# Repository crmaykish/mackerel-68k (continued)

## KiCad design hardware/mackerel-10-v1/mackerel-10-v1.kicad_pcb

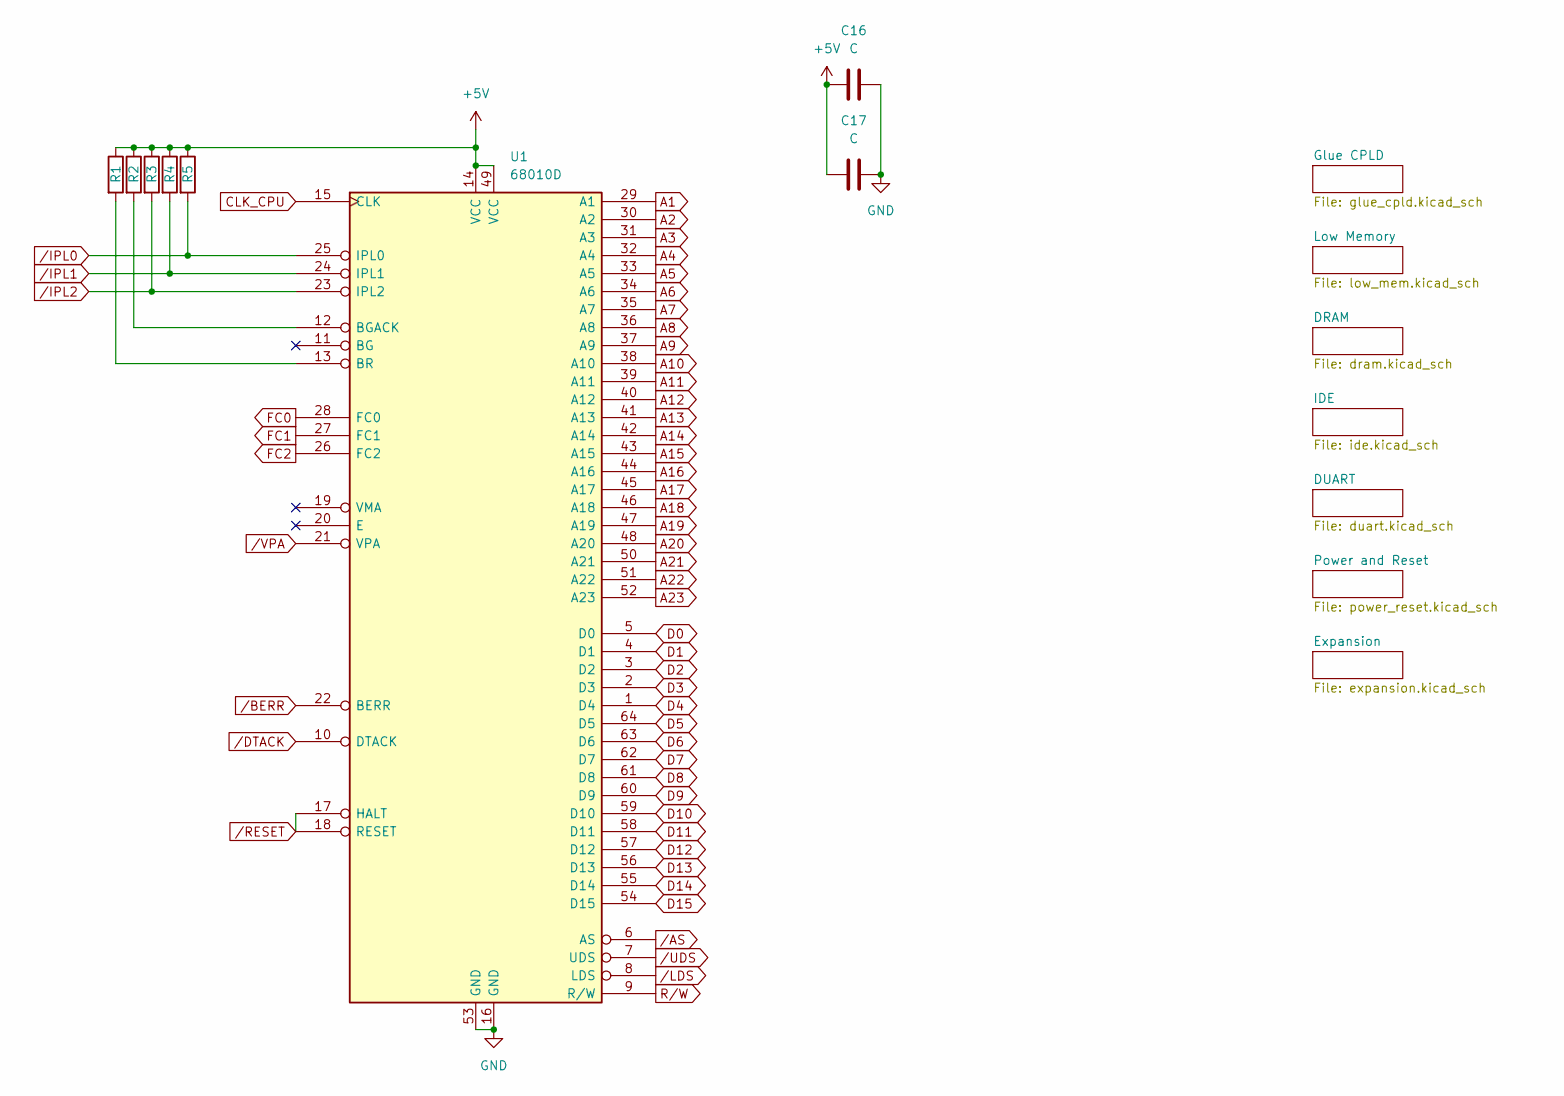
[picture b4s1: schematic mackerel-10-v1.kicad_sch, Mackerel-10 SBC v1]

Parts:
C16, C17: C; C_Disc_D4.3mm_W1.9mm_P5.00mm
R1, R2, R3, R4, R5: R; R_Axial_DIN0207_L6.3mm_D2.5mm_P7.62mm_Horizontal
U1: 68010D; DIP-64_W22.86mm

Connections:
+5V: C16.1, C17.1, R1.1, R2.1, R3.1, R4.1, R5.1, U1.14 (VCC), U1.49 (VCC); also elsewhere on the board
A1: U1.29 (A1); also elsewhere on the board
A2: U1.30 (A2); also elsewhere on the board
A3: U1.31 (A3); also elsewhere on the board
A4: U1.32 (A4); also elsewhere on the board
A5: U1.33 (A5); also elsewhere on the board
A6: U1.34 (A6); also elsewhere on the board
A7: U1.35 (A7); also elsewhere on the board
A8: U1.36 (A8); also elsewhere on the board
A9: U1.37 (A9); also elsewhere on the board
A10: U1.38 (A10); also elsewhere on the board
A11: U1.39 (A11); also elsewhere on the board
A12: U1.40 (A12); also elsewhere on the board
A13: U1.41 (A13); also elsewhere on the board
A14: U1.42 (A14); also elsewhere on the board
A15: U1.43 (A15); also elsewhere on the board
A16: U1.44 (A16); also elsewhere on the board
A17: U1.45 (A17); also elsewhere on the board
A18: U1.46 (A18); also elsewhere on the board
A19: U1.47 (A19); also elsewhere on the board
A20: U1.48 (A20); also elsewhere on the board
A21: U1.50 (A21); also elsewhere on the board
A22: U1.51 (A22); also elsewhere on the board
A23: U1.52 (A23); also elsewhere on the board
CLK_CPU: U1.15 (CLK); also elsewhere on the board
D0: U1.5 (D0); also elsewhere on the board
D1: U1.4 (D1); also elsewhere on the board
D2: U1.3 (D2); also elsewhere on the board
D3: U1.2 (D3); also elsewhere on the board
D4: U1.1 (D4); also elsewhere on the board
D5: U1.64 (D5); also elsewhere on the board
D6: U1.63 (D6); also elsewhere on the board
D7: U1.62 (D7); also elsewhere on the board
D8: U1.61 (D8); also elsewhere on the board
D9: U1.60 (D9); also elsewhere on the board
D10: U1.59 (D10); also elsewhere on the board
D11: U1.58 (D11); also elsewhere on the board
D12: U1.57 (D12); also elsewhere on the board
D13: U1.56 (D13); also elsewhere on the board
D14: U1.55 (D14); also elsewhere on the board
D15: U1.54 (D15); also elsewhere on the board
FC0: U1.28 (FC0); also elsewhere on the board
FC1: U1.27 (FC1); also elsewhere on the board
FC2: U1.26 (FC2); also elsewhere on the board
GND: C16.2, C17.2, U1.16 (GND), U1.53 (GND); also elsewhere on the board
unnamed: R2.2, U1.12 (BGACK)
unnamed: R1.2, U1.13 (BR)
R/W: U1.9 (R/W); also elsewhere on the board
/AS: U1.6 (AS); also elsewhere on the board
/BERR: U1.22 (BERR); also elsewhere on the board
/DTACK: U1.10 (DTACK); also elsewhere on the board
/IPL0: R5.2, U1.25 (IPL0); also elsewhere on the board
/IPL1: R4.2, U1.24 (IPL1); also elsewhere on the board
/IPL2: R3.2, U1.23 (IPL2); also elsewhere on the board
/LDS: U1.8 (LDS); also elsewhere on the board
/RESET: U1.17 (HALT), U1.18 (RESET); also elsewhere on the board
/UDS: U1.7 (UDS); also elsewhere on the board
/VPA: U1.21 (VPA); also elsewhere on the board

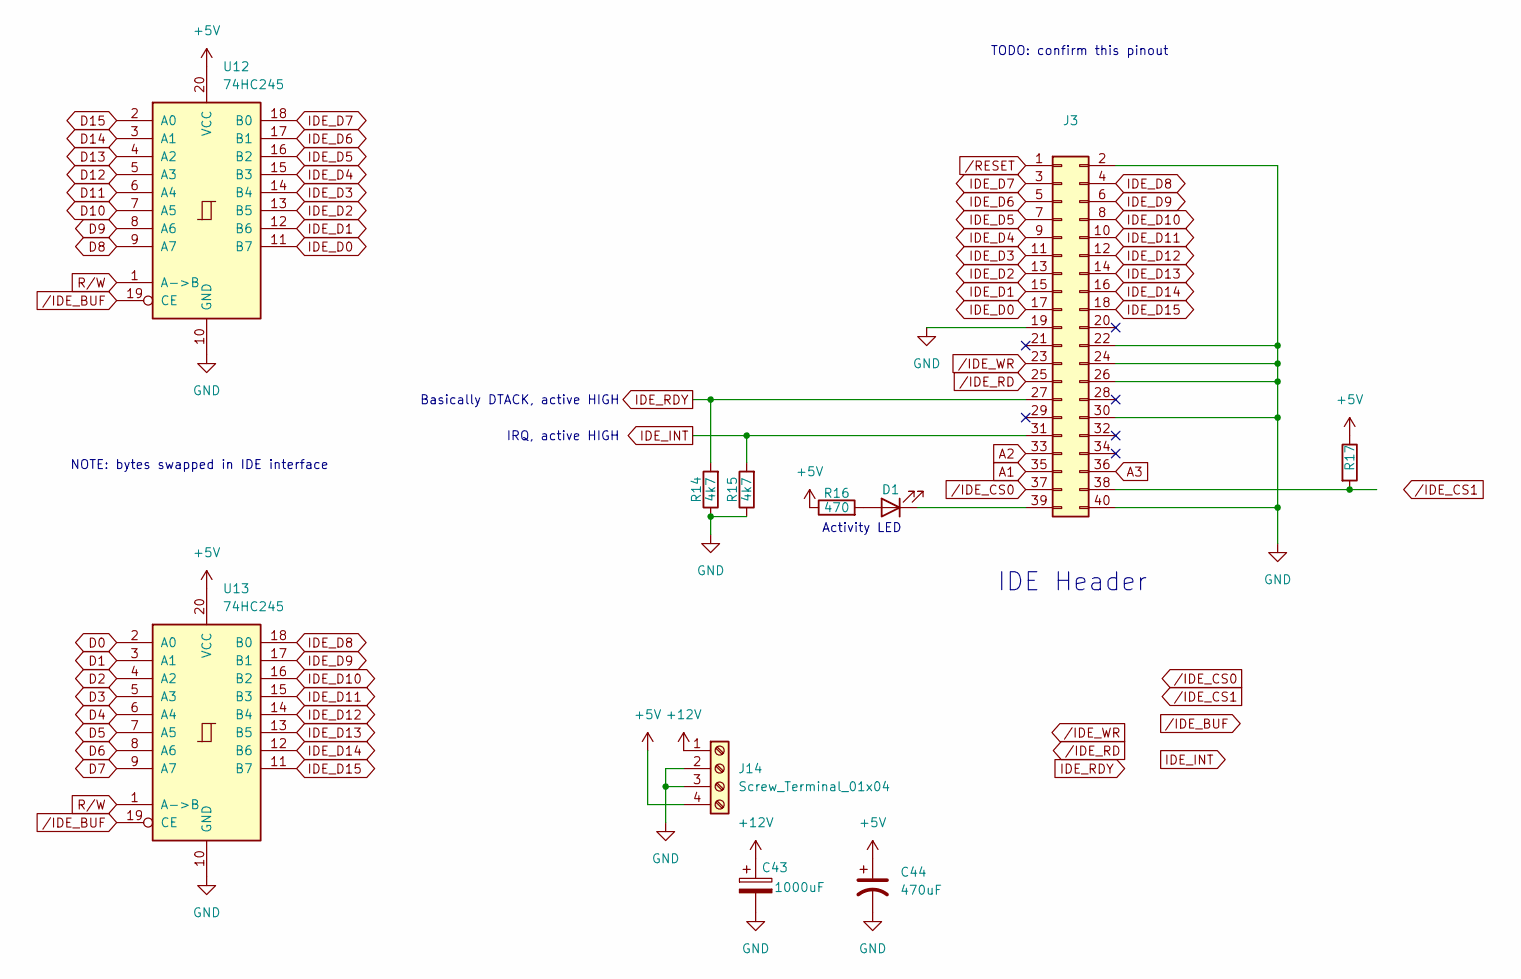
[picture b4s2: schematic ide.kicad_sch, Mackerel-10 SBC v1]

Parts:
C43: 1000uF; CP_Radial_D10.0mm_P5.00mm
C44: 470uF; CP_Radial_D8.0mm_P3.50mm
D1: LED; LED_D5.0mm
J3: Conn_02x20_Odd_Even; IDC-Header_2x20_P2.54mm_Vertical
J14: Screw_Terminal_01x04; TerminalBlock_bornier-4_P5.08mm
R14, R15: 4k7; R_Axial_DIN0207_L6.3mm_D2.5mm_P7.62mm_Horizontal
R16: 470; R_Axial_DIN0207_L6.3mm_D2.5mm_P7.62mm_Horizontal
R17: R; R_Axial_DIN0207_L6.3mm_D2.5mm_P7.62mm_Horizontal
U12, U13: 74HC245; DIP-20_W7.62mm_Socket

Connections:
+5V: C44.1, J14.4, R16.1, R17.1, U12.20 (VCC), U13.20 (VCC); also elsewhere on the board
+12V: C43.1, J14.1; also elsewhere on the board
A1: J3.35; also elsewhere on the board
A2: J3.33; also elsewhere on the board
A3: J3.36; also elsewhere on the board
D0: U13.2 (A0); also elsewhere on the board
D1: U13.3 (A1); also elsewhere on the board
D2: U13.4 (A2); also elsewhere on the board
D3: U13.5 (A3); also elsewhere on the board
D4: U13.6 (A4); also elsewhere on the board
D5: U13.7 (A5); also elsewhere on the board
D6: U13.8 (A6); also elsewhere on the board
D7: U13.9 (A7); also elsewhere on the board
D8: U12.9 (A7); also elsewhere on the board
D9: U12.8 (A6); also elsewhere on the board
D10: U12.7 (A5); also elsewhere on the board
D11: U12.6 (A4); also elsewhere on the board
D12: U12.5 (A3); also elsewhere on the board
D13: U12.4 (A2); also elsewhere on the board
D14: U12.3 (A1); also elsewhere on the board
D15: U12.2 (A0); also elsewhere on the board
GND: C43.2, C44.2, J3.2, J3.19, J3.22, J3.24, J3.26, J3.30, J3.40, J14.2, J14.3, R14.1, R15.1, U12.10 (GND), U13.10 (GND); also elsewhere on the board
IDE_D0: J3.17, U12.11 (B7)
IDE_D1: J3.15, U12.12 (B6)
IDE_D2: J3.13, U12.13 (B5)
IDE_D3: J3.11, U12.14 (B4)
IDE_D4: J3.9, U12.15 (B3)
IDE_D5: J3.7, U12.16 (B2)
IDE_D6: J3.5, U12.17 (B1)
IDE_D7: J3.3, U12.18 (B0)
IDE_D8: J3.4, U13.18 (B0)
IDE_D9: J3.6, U13.17 (B1)
IDE_D10: J3.8, U13.16 (B2)
IDE_D11: J3.10, U13.15 (B3)
IDE_D12: J3.12, U13.14 (B4)
IDE_D13: J3.14, U13.13 (B5)
IDE_D14: J3.16, U13.12 (B6)
IDE_D15: J3.18, U13.11 (B7)
IDE_INT: J3.31, R15.2
IDE_RDY: J3.27, R14.2
unnamed: D1.2 (A), R16.2
unnamed: D1.1 (K), J3.39
unnamed: J3.38, R17.2
R/W: U12.1 (A->B), U13.1 (A->B); also elsewhere on the board
/IDE_BUF: U12.19 (CE), U13.19 (CE)
/IDE_CS0: J3.37
/IDE_RD: J3.25
/IDE_WR: J3.23
/RESET: J3.1; also elsewhere on the board

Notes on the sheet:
IDE Header
Basically DTACK, active HIGH
NOTE: bytes swapped in IDE interface
TODO: confirm this pinout
Activity LED
IRQ, active HIGH

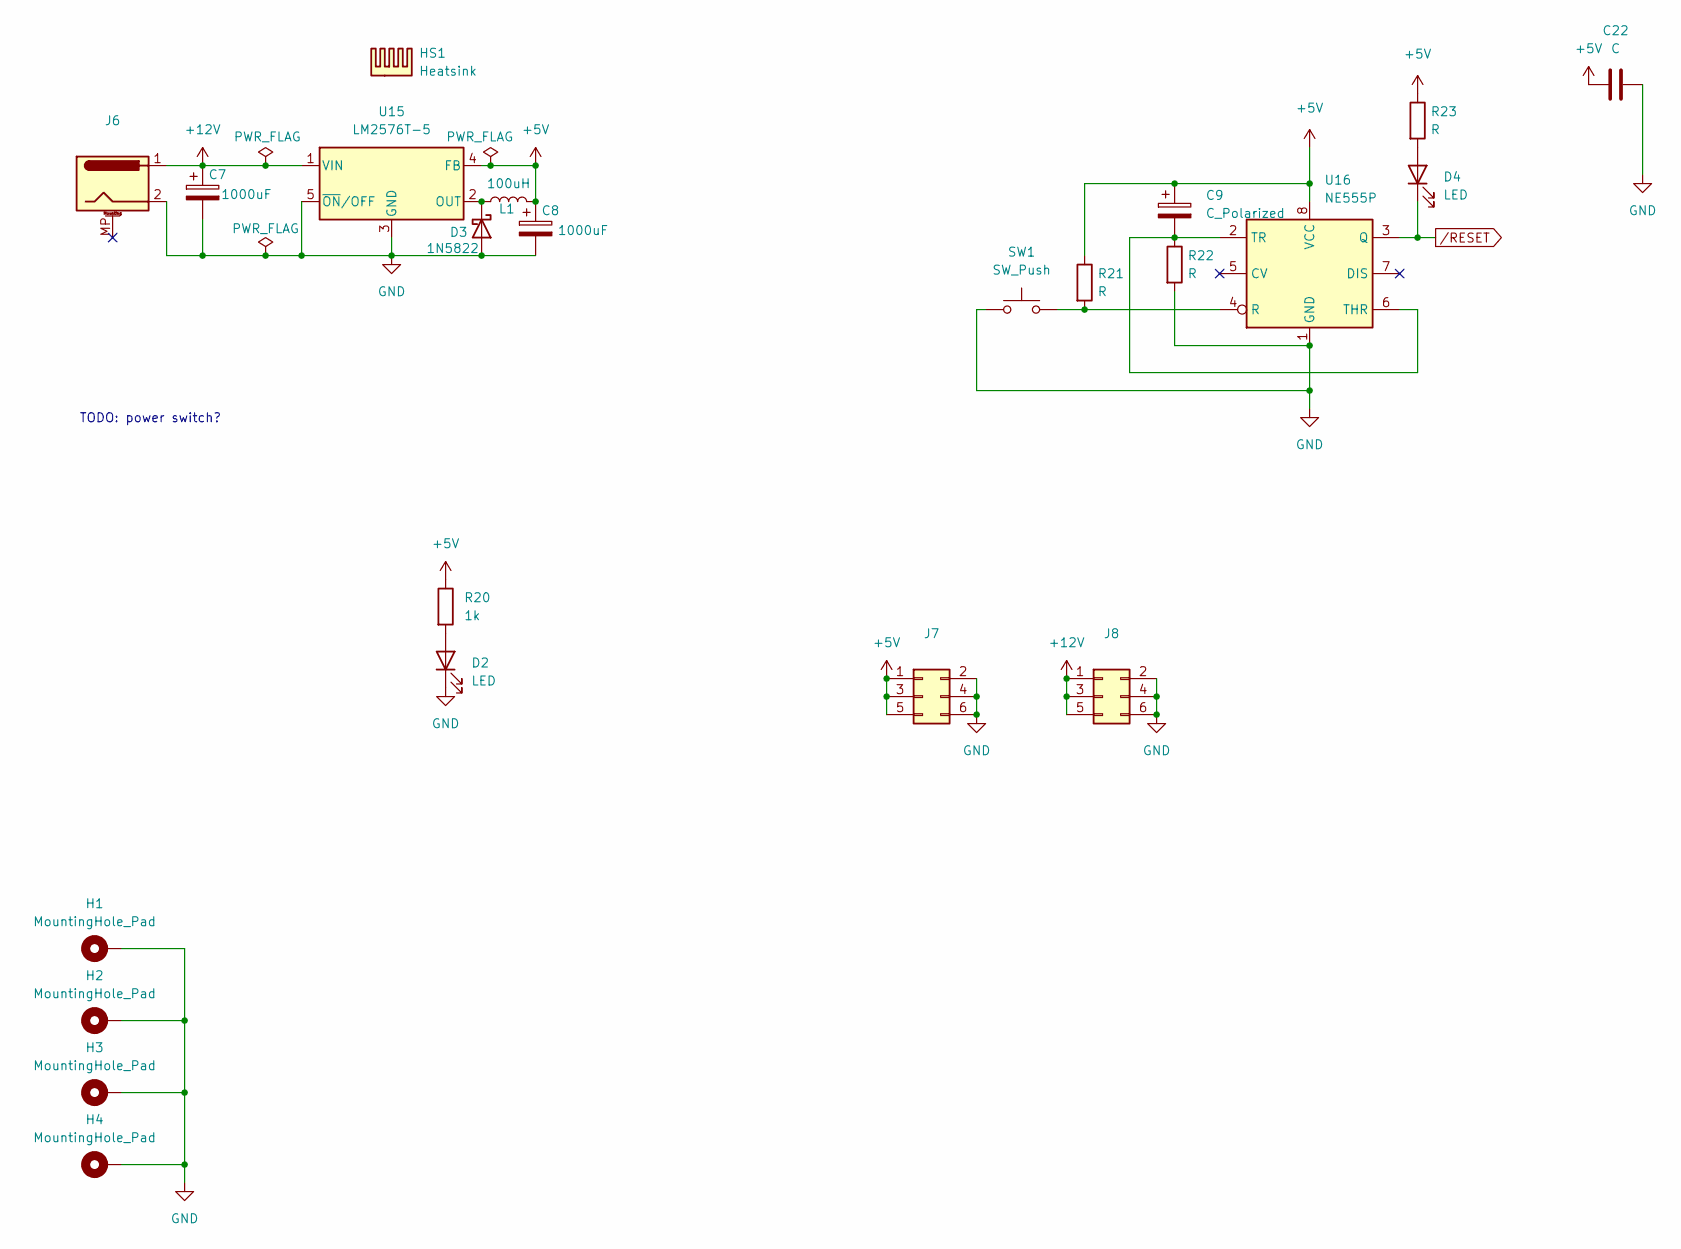
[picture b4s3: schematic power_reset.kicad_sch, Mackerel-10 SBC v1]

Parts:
C7, C8: 1000uF; CP_Radial_D10.0mm_P5.00mm
C9: C_Polarized; CP_Radial_D5.0mm_P2.50mm
C22: C; C_Disc_D4.3mm_W1.9mm_P5.00mm
D2, D4: LED; LED_D5.0mm
D3: 1N5822; D_DO-27_P15.24mm_Horizontal
H1, H2, H3, H4: MountingHole_Pad; MountingHole_3.2mm_M3_Pad_Via
HS1: Heatsink; Heatsink_Stonecold_HS-S02_13.21x9.53mm
J6: Barrel_Jack_MountingPin; BarrelJack_Horizontal
J7, J8: Conn_02x03_Odd_Even; PinHeader_2x03_P2.54mm_Vertical
L1: 100uH; L_Radial_D10.0mm_P5.00mm_Fastron_07M
R20: 1k; R_Axial_DIN0207_L6.3mm_D2.5mm_P7.62mm_Horizontal
R21, R22, R23: R; R_Axial_DIN0207_L6.3mm_D2.5mm_P7.62mm_Horizontal
SW1: SW_Push; SW_PUSH_6mm_H5mm
U15: LM2576T-5; TO-220-5_Vertical
U16: NE555P; DIP-8_W7.62mm

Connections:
+5V: C8.1, C9.1, C22.1, J7.1, J7.3, J7.5, L1.2, R20.1, R21.1, R23.1, U15.4 (FB), U16.8 (VCC); also elsewhere on the board
+12V: C7.1, J6.1, J8.1, J8.3, J8.5, U15.1 (VIN); also elsewhere on the board
GND: C7.2, C8.2, C22.2, D2.1 (K), D3.2 (A), H1.1, H2.1, H3.1, H4.1, J6.2, J7.2, J7.4, J7.6, J8.2, J8.4, J8.6, R22.2, SW1.1, U15.3 (GND), U15.5 (~ON/OFF), U16.1 (GND); also elsewhere on the board
unnamed: D2.2 (A), R20.2
unnamed: D3.1 (K), L1.1, U15.2 (OUT)
unnamed: D4.2 (A), R23.2
unnamed: R21.2, SW1.2, U16.4 (R)
unnamed: C9.2, R22.1, U16.2 (TR), U16.6 (THR)
/RESET: D4.1 (K), U16.3 (Q); also elsewhere on the board

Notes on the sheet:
TODO: power switch?

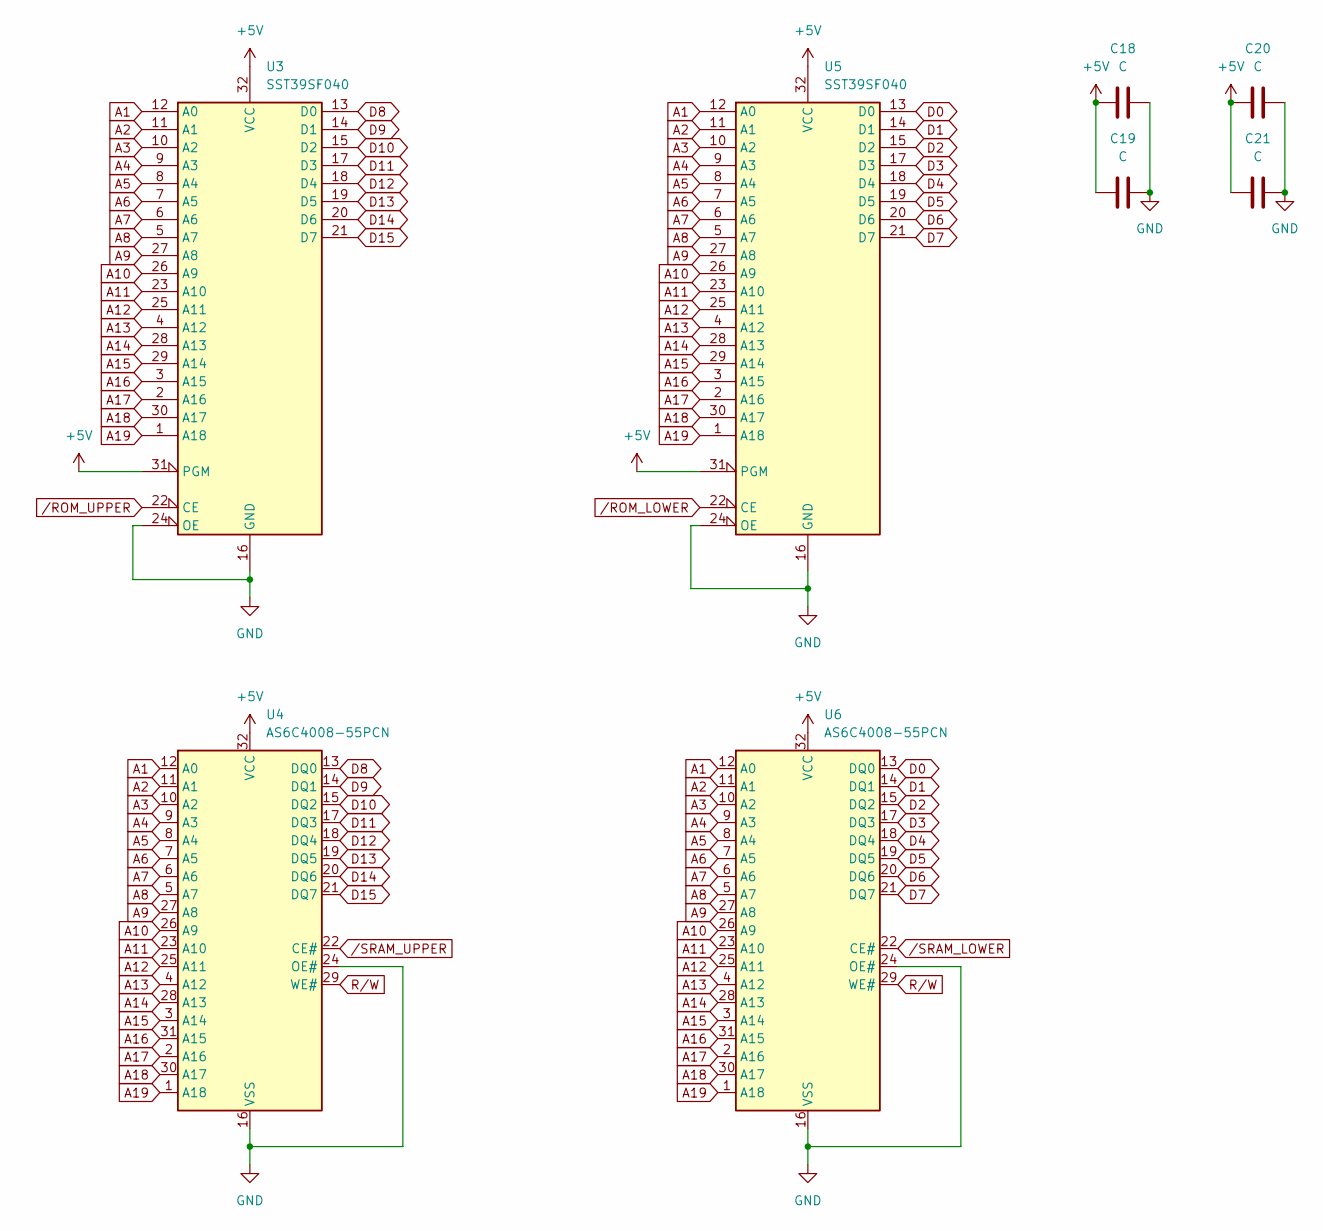
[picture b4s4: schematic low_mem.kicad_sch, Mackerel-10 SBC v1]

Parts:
C18, C19, C20, C21: C; C_Disc_D4.3mm_W1.9mm_P5.00mm
U3, U5: SST39SF040; DIP-32_W15.24mm
U4, U6: AS6C4008-55PCN; DIP-32_W15.24mm

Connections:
+5V: C18.1, C19.1, C20.1, C21.1, U3.31 (PGM), U3.32 (VCC), U4.32 (VCC), U5.31 (PGM), U5.32 (VCC), U6.32 (VCC); also elsewhere on the board
A1: U3.12 (A0), U4.12 (A0), U5.12 (A0), U6.12 (A0); also elsewhere on the board
A2: U3.11 (A1), U4.11 (A1), U5.11 (A1), U6.11 (A1); also elsewhere on the board
A3: U3.10 (A2), U4.10 (A2), U5.10 (A2), U6.10 (A2); also elsewhere on the board
A4: U3.9 (A3), U4.9 (A3), U5.9 (A3), U6.9 (A3); also elsewhere on the board
A5: U3.8 (A4), U4.8 (A4), U5.8 (A4), U6.8 (A4); also elsewhere on the board
A6: U3.7 (A5), U4.7 (A5), U5.7 (A5), U6.7 (A5); also elsewhere on the board
A7: U3.6 (A6), U4.6 (A6), U5.6 (A6), U6.6 (A6); also elsewhere on the board
A8: U3.5 (A7), U4.5 (A7), U5.5 (A7), U6.5 (A7); also elsewhere on the board
A9: U3.27 (A8), U4.27 (A8), U5.27 (A8), U6.27 (A8); also elsewhere on the board
A10: U3.26 (A9), U4.26 (A9), U5.26 (A9), U6.26 (A9); also elsewhere on the board
A11: U3.23 (A10), U4.23 (A10), U5.23 (A10), U6.23 (A10); also elsewhere on the board
A12: U3.25 (A11), U4.25 (A11), U5.25 (A11), U6.25 (A11); also elsewhere on the board
A13: U3.4 (A12), U4.4 (A12), U5.4 (A12), U6.4 (A12); also elsewhere on the board
A14: U3.28 (A13), U4.28 (A13), U5.28 (A13), U6.28 (A13); also elsewhere on the board
A15: U3.29 (A14), U4.3 (A14), U5.29 (A14), U6.3 (A14); also elsewhere on the board
A16: U3.3 (A15), U4.31 (A15), U5.3 (A15), U6.31 (A15); also elsewhere on the board
A17: U3.2 (A16), U4.2 (A16), U5.2 (A16), U6.2 (A16); also elsewhere on the board
A18: U3.30 (A17), U4.30 (A17), U5.30 (A17), U6.30 (A17); also elsewhere on the board
A19: U3.1 (A18), U4.1 (A18), U5.1 (A18), U6.1 (A18); also elsewhere on the board
D0: U5.13 (D0), U6.13 (DQ0); also elsewhere on the board
D1: U5.14 (D1), U6.14 (DQ1); also elsewhere on the board
D2: U5.15 (D2), U6.15 (DQ2); also elsewhere on the board
D3: U5.17 (D3), U6.17 (DQ3); also elsewhere on the board
D4: U5.18 (D4), U6.18 (DQ4); also elsewhere on the board
D5: U5.19 (D5), U6.19 (DQ5); also elsewhere on the board
D6: U5.20 (D6), U6.20 (DQ6); also elsewhere on the board
D7: U5.21 (D7), U6.21 (DQ7); also elsewhere on the board
D8: U3.13 (D0), U4.13 (DQ0); also elsewhere on the board
D9: U3.14 (D1), U4.14 (DQ1); also elsewhere on the board
D10: U3.15 (D2), U4.15 (DQ2); also elsewhere on the board
D11: U3.17 (D3), U4.17 (DQ3); also elsewhere on the board
D12: U3.18 (D4), U4.18 (DQ4); also elsewhere on the board
D13: U3.19 (D5), U4.19 (DQ5); also elsewhere on the board
D14: U3.20 (D6), U4.20 (DQ6); also elsewhere on the board
D15: U3.21 (D7), U4.21 (DQ7); also elsewhere on the board
GND: C18.2, C19.2, C20.2, C21.2, U3.16 (GND), U3.24 (OE), U4.16 (VSS), U4.24 (OE#), U5.16 (GND), U5.24 (OE), U6.16 (VSS), U6.24 (OE#); also elsewhere on the board
R/W: U4.29 (WE#), U6.29 (WE#); also elsewhere on the board
/ROM_LOWER: U5.22 (CE); also elsewhere on the board
/ROM_UPPER: U3.22 (CE); also elsewhere on the board
/SRAM_LOWER: U6.22 (CE#); also elsewhere on the board
/SRAM_UPPER: U4.22 (CE#); also elsewhere on the board

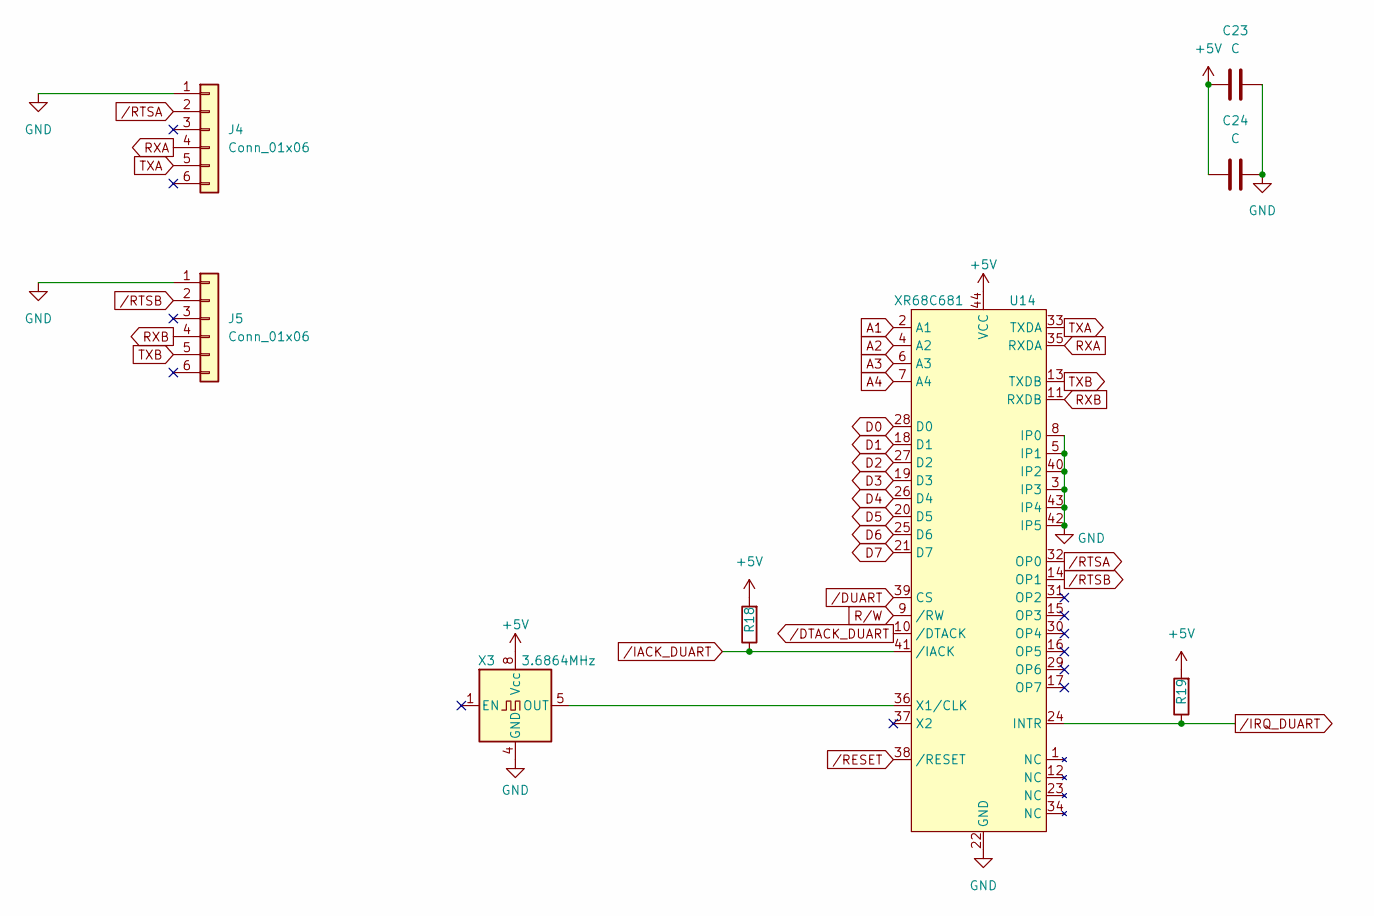
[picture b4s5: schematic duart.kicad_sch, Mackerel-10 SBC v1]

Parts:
C23, C24: C; C_Disc_D4.3mm_W1.9mm_P5.00mm
J4, J5: Conn_01x06; PinSocket_1x06_P2.54mm_Vertical
R18, R19: R; R_Axial_DIN0207_L6.3mm_D2.5mm_P7.62mm_Horizontal
U14: XR68C681; PLCC-44_THT-Socket
X3: 3.6864MHz; Oscillator_DIP-8

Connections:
+5V: C23.1, C24.1, R18.2, R19.2, U14.44 (VCC), X3.8 (Vcc); also elsewhere on the board
A1: U14.2 (A1); also elsewhere on the board
A2: U14.4 (A2); also elsewhere on the board
A3: U14.6 (A3); also elsewhere on the board
A4: U14.7 (A4); also elsewhere on the board
D0: U14.28 (D0); also elsewhere on the board
D1: U14.18 (D1); also elsewhere on the board
D2: U14.27 (D2); also elsewhere on the board
D3: U14.19 (D3); also elsewhere on the board
D4: U14.26 (D4); also elsewhere on the board
D5: U14.20 (D5); also elsewhere on the board
D6: U14.25 (D6); also elsewhere on the board
D7: U14.21 (D7); also elsewhere on the board
GND: C23.2, C24.2, J4.1, J5.1, U14.3 (IP3), U14.5 (IP1), U14.8 (IP0), U14.22 (GND), U14.40 (IP2), U14.42 (IP5), U14.43 (IP4), X3.4 (GND); also elsewhere on the board
unnamed: U14.36 (X1/CLK), X3.5 (OUT)
RXA: J4.4, U14.35 (RXDA)
RXB: J5.4, U14.11 (RXDB)
R/W: U14.9 (/RW); also elsewhere on the board
TXA: J4.5, U14.33 (TXDA)
TXB: J5.5, U14.13 (TXDB)
/DTACK_DUART: U14.10 (/DTACK); also elsewhere on the board
/DUART: U14.39 (CS); also elsewhere on the board
/IACK_DUART: R18.1, U14.41 (/IACK); also elsewhere on the board
/IRQ_DUART: R19.1, U14.24 (INTR); also elsewhere on the board
/RESET: U14.38 (/RESET); also elsewhere on the board
/RTSA: J4.2, U14.32 (OP0)
/RTSB: J5.2, U14.14 (OP1)

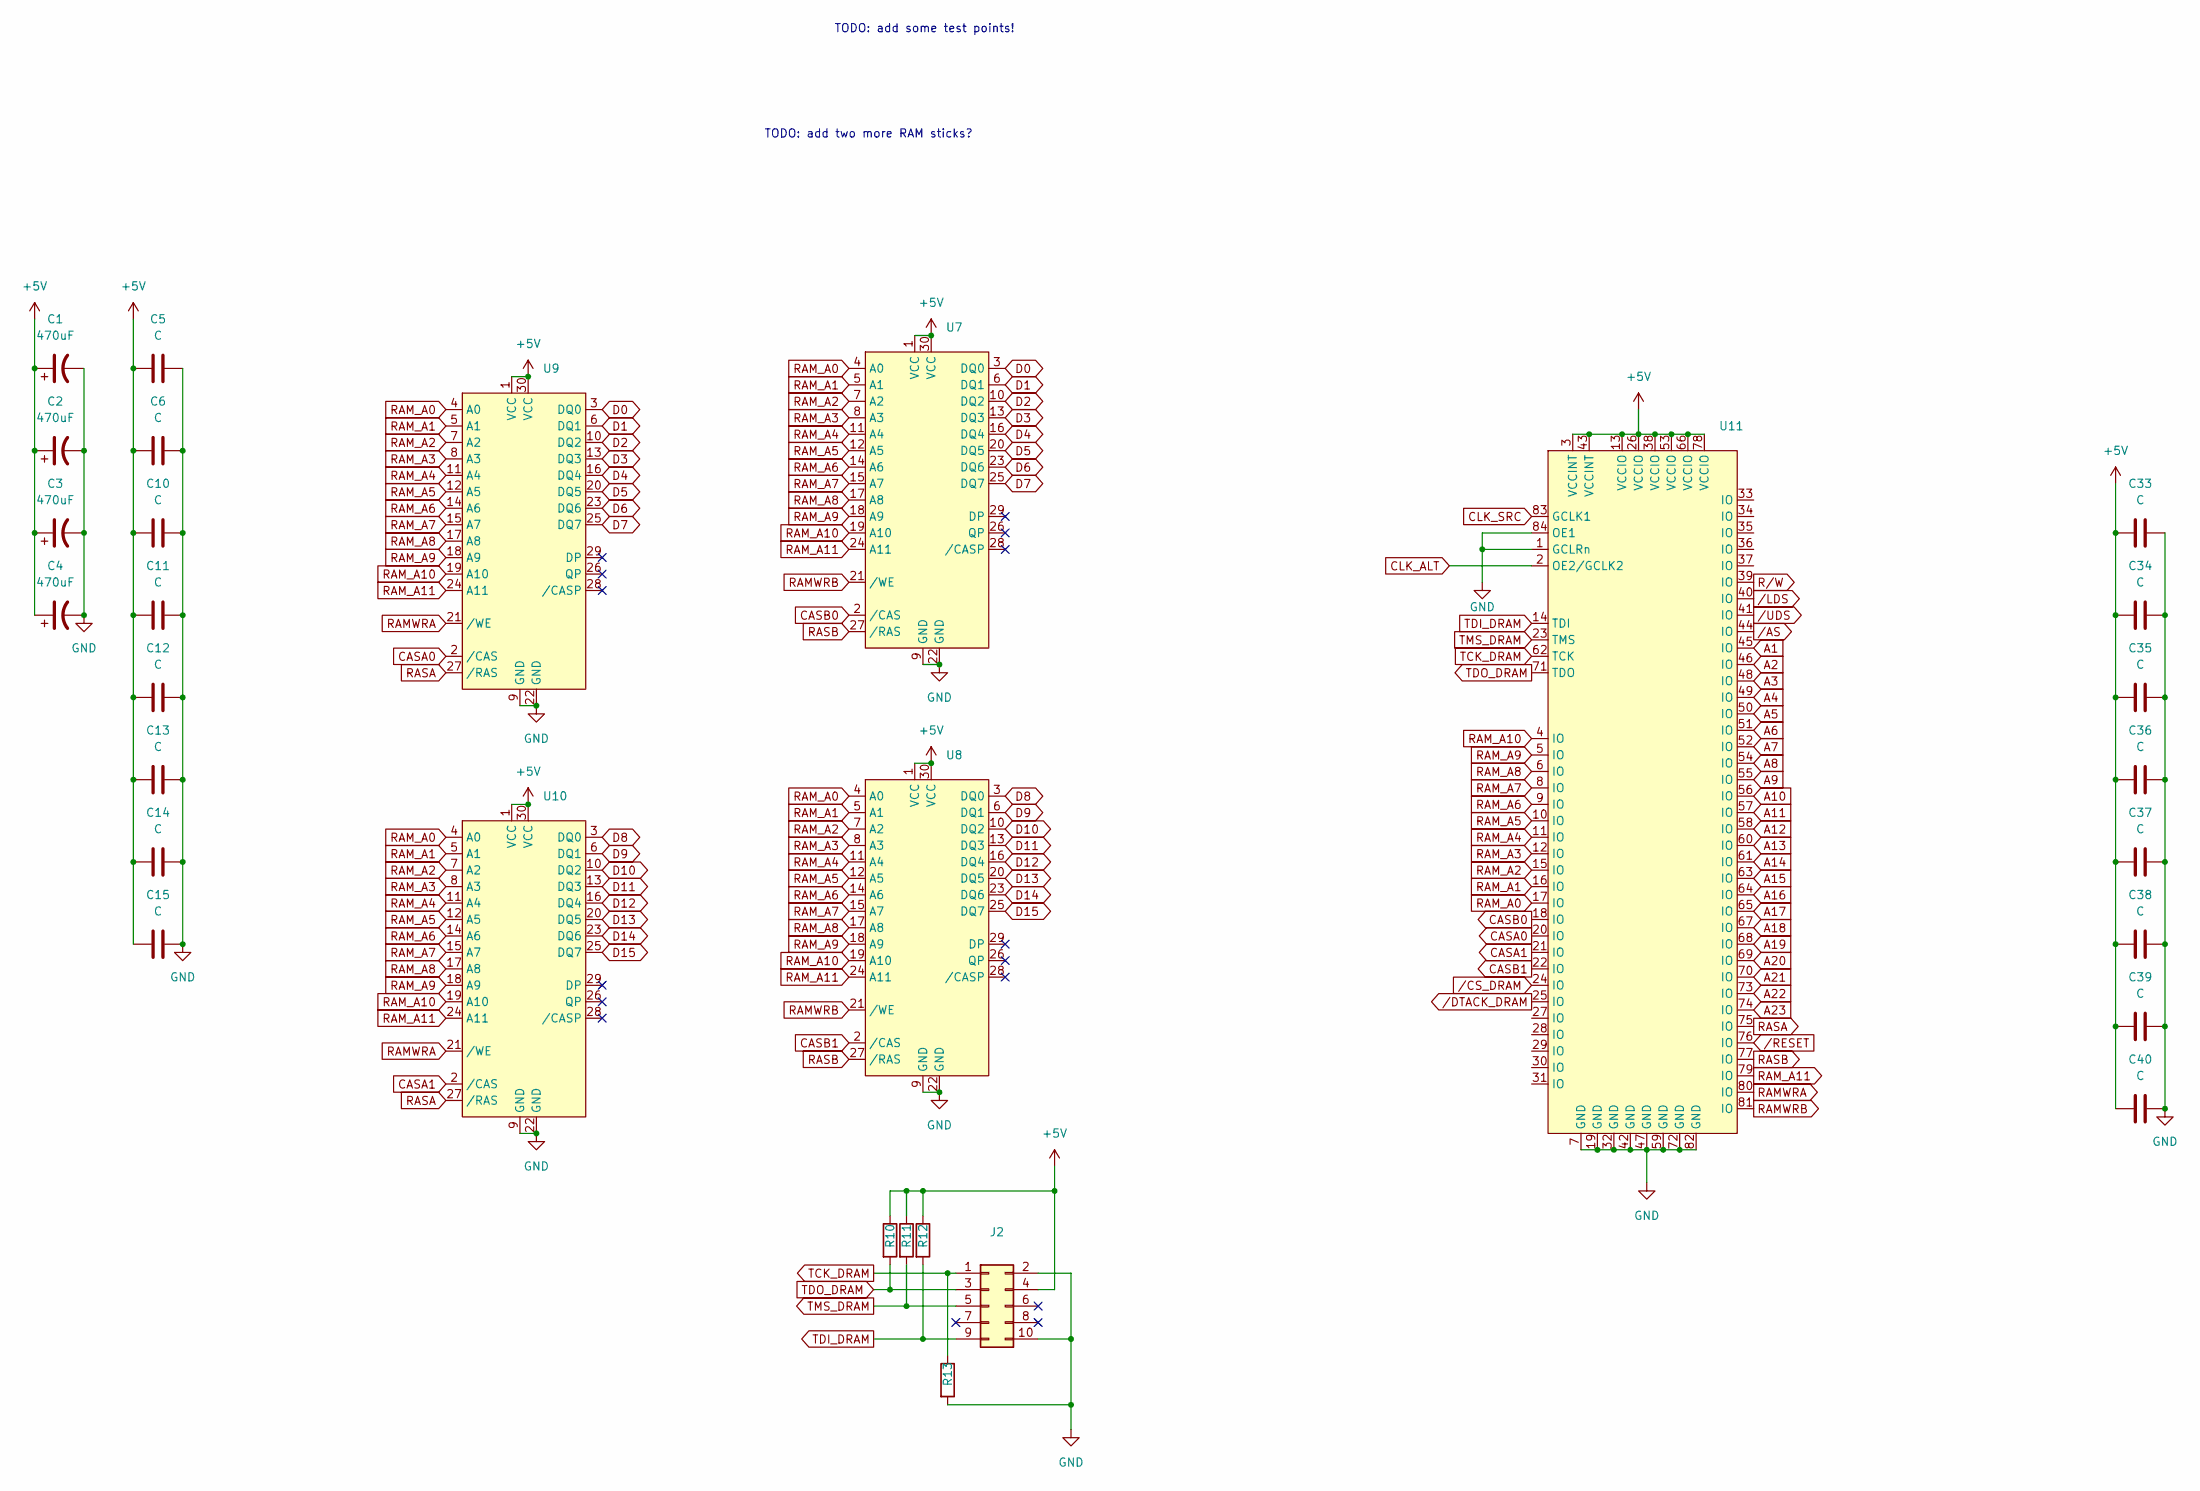
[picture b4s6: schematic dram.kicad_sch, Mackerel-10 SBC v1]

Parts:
C1, C2, C3, C4: 470uF; CP_Radial_D8.0mm_P3.50mm
C5, C6, C10, C11, C12, C13, C14, C15, C33, C34, C35, C36, C37, C38, C39, C40: C; C_Disc_D4.3mm_W1.9mm_P5.00mm
J2: Conn_02x05_Odd_Even; IDC-Header_2x05_P2.54mm_Vertical
R10, R11, R12, R13: R; R_Axial_DIN0207_L6.3mm_D2.5mm_P7.62mm_Horizontal
U7, U8, U9, U10: SIMM-30
U11: PLCC-84_THT-Socket

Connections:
+5V: C1.1, C2.1, C3.1, C4.1, C5.1, C6.1, C10.1, C11.1, C12.2, C13.2, C14.2, C15.2, C33.1, C34.1, C35.1, C36.1, C37.2, C38.2, C39.2, C40.2, J2.4, R10.1, R11.1, R12.1, U7.1 (VCC), U7.30 (VCC), U8.1 (VCC), U8.30 (VCC), U9.1 (VCC), U9.30 (VCC), U10.1 (VCC), U10.30 (VCC), U11.3 (VCCINT), U11.13 (VCCIO), U11.26 (VCCIO), U11.38 (VCCIO), U11.43 (VCCINT), U11.53 (VCCIO), U11.66 (VCCIO), U11.78 (VCCIO); also elsewhere on the board
A1: U11.45 (IO); also elsewhere on the board
A2: U11.46 (IO); also elsewhere on the board
A3: U11.48 (IO); also elsewhere on the board
A4: U11.49 (IO); also elsewhere on the board
A5: U11.50 (IO); also elsewhere on the board
A6: U11.51 (IO); also elsewhere on the board
A7: U11.52 (IO); also elsewhere on the board
A8: U11.54 (IO); also elsewhere on the board
A9: U11.55 (IO); also elsewhere on the board
A10: U11.56 (IO); also elsewhere on the board
A11: U11.57 (IO); also elsewhere on the board
A12: U11.58 (IO); also elsewhere on the board
A13: U11.60 (IO); also elsewhere on the board
A14: U11.61 (IO); also elsewhere on the board
A15: U11.63 (IO); also elsewhere on the board
A16: U11.64 (IO); also elsewhere on the board
A17: U11.65 (IO); also elsewhere on the board
A18: U11.67 (IO); also elsewhere on the board
A19: U11.68 (IO); also elsewhere on the board
A20: U11.69 (IO); also elsewhere on the board
A21: U11.70 (IO); also elsewhere on the board
A22: U11.73 (IO); also elsewhere on the board
A23: U11.74 (IO); also elsewhere on the board
CASA0: U9.2 (/CAS), U11.20 (IO)
CASA1: U10.2 (/CAS), U11.21 (IO)
CASB0: U7.2 (/CAS), U11.18 (IO)
CASB1: U8.2 (/CAS), U11.22 (IO)
CLK_ALT: U11.2 (OE2/GCLK2); also elsewhere on the board
CLK_SRC: U11.83 (GCLK1); also elsewhere on the board
D0: U7.3 (DQ0), U9.3 (DQ0); also elsewhere on the board
D1: U7.6 (DQ1), U9.6 (DQ1); also elsewhere on the board
D2: U7.10 (DQ2), U9.10 (DQ2); also elsewhere on the board
D3: U7.13 (DQ3), U9.13 (DQ3); also elsewhere on the board
D4: U7.16 (DQ4), U9.16 (DQ4); also elsewhere on the board
D5: U7.20 (DQ5), U9.20 (DQ5); also elsewhere on the board
D6: U7.23 (DQ6), U9.23 (DQ6); also elsewhere on the board
D7: U7.25 (DQ7), U9.25 (DQ7); also elsewhere on the board
D8: U8.3 (DQ0), U10.3 (DQ0); also elsewhere on the board
D9: U8.6 (DQ1), U10.6 (DQ1); also elsewhere on the board
D10: U8.10 (DQ2), U10.10 (DQ2); also elsewhere on the board
D11: U8.13 (DQ3), U10.13 (DQ3); also elsewhere on the board
D12: U8.16 (DQ4), U10.16 (DQ4); also elsewhere on the board
D13: U8.20 (DQ5), U10.20 (DQ5); also elsewhere on the board
D14: U8.23 (DQ6), U10.23 (DQ6); also elsewhere on the board
D15: U8.25 (DQ7), U10.25 (DQ7); also elsewhere on the board
GND: C1.2, C2.2, C3.2, C4.2, C5.2, C6.2, C10.2, C11.2, C12.1, C13.1, C14.1, C15.1, C33.2, C34.2, C35.2, C36.2, C37.1, C38.1, C39.1, C40.1, J2.2, J2.10, R13.2, U7.9 (GND), U7.22 (GND), U8.9 (GND), U8.22 (GND), U9.9 (GND), U9.22 (GND), U10.9 (GND), U10.22 (GND), U11.1 (GCLRn), U11.7 (GND), U11.19 (GND), U11.32 (GND), U11.42 (GND), U11.47 (GND), U11.59 (GND), U11.72 (GND), U11.82 (GND), U11.84 (OE1); also elsewhere on the board
RAMWRA: U9.21 (/WE), U10.21 (/WE), U11.80 (IO)
RAMWRB: U7.21 (/WE), U8.21 (/WE), U11.81 (IO)
RAM_A0: U7.4 (A0), U8.4 (A0), U9.4 (A0), U10.4 (A0), U11.17 (IO)
RAM_A1: U7.5 (A1), U8.5 (A1), U9.5 (A1), U10.5 (A1), U11.16 (IO)
RAM_A2: U7.7 (A2), U8.7 (A2), U9.7 (A2), U10.7 (A2), U11.15 (IO)
RAM_A3: U7.8 (A3), U8.8 (A3), U9.8 (A3), U10.8 (A3), U11.12 (IO)
RAM_A4: U7.11 (A4), U8.11 (A4), U9.11 (A4), U10.11 (A4), U11.11 (IO)
RAM_A5: U7.12 (A5), U8.12 (A5), U9.12 (A5), U10.12 (A5), U11.10 (IO)
RAM_A6: U7.14 (A6), U8.14 (A6), U9.14 (A6), U10.14 (A6), U11.9 (IO)
RAM_A7: U7.15 (A7), U8.15 (A7), U9.15 (A7), U10.15 (A7), U11.8 (IO)
RAM_A8: U7.17 (A8), U8.17 (A8), U9.17 (A8), U10.17 (A8), U11.6 (IO)
RAM_A9: U7.18 (A9), U8.18 (A9), U9.18 (A9), U10.18 (A9), U11.5 (IO)
RAM_A10: U7.19 (A10), U8.19 (A10), U9.19 (A10), U10.19 (A10), U11.4 (IO)
RAM_A11: U7.24 (A11), U8.24 (A11), U9.24 (A11), U10.24 (A11), U11.79 (IO)
RASA: U9.27 (/RAS), U10.27 (/RAS), U11.75 (IO)
RASB: U7.27 (/RAS), U8.27 (/RAS), U11.77 (IO)
R/W: U11.39 (IO); also elsewhere on the board
TCK_DRAM: J2.1, R13.1, U11.62 (TCK)
TDI_DRAM: J2.9, R12.2, U11.14 (TDI)
TDO_DRAM: J2.3, R10.2, U11.71 (TDO)
TMS_DRAM: J2.5, R11.2, U11.23 (TMS)
/AS: U11.44 (IO); also elsewhere on the board
/CS_DRAM: U11.24 (IO); also elsewhere on the board
/DTACK_DRAM: U11.25 (IO); also elsewhere on the board
/LDS: U11.40 (IO); also elsewhere on the board
/RESET: U11.76 (IO); also elsewhere on the board
/UDS: U11.41 (IO); also elsewhere on the board

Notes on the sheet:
TODO: add some test points!
TODO: add two more RAM sticks?
